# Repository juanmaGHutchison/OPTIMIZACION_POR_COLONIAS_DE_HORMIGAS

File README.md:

# Proyecto Final de Carrera: Diseño y Fabricación de Robots basados en Arduino para realizar el Algoritmo de Colonias de Hormigas.

_El proyecto permite realizar una ejecución real del Algoritmo de Colonias de Hormigas en un robot diseñado y fabricado en Arduino, diseño del robot disponible en el mismo proyecto._

Podemos encontrar una breve explicación además de una ejecución del robot finalizado en el siguiente enlace:
* [Ejecución ACO en Arduino](https://www.youtube.com/watch?v=iJVlAWncoFY&t=352s) - Video explicativo con posterior ejecución del Algoritmo de Colonias de Hormigas.

Y tenemos otro video en el cual se detalla el montaje de dicho robot en Arduino:
* [Montaje robot ACO](https://www.youtube.com/watch?v=88lnHN8jg98) - Video explicativo del montaje del robot en Arduino.

## Descripcion de directorios y archivos

_Descripción de los directorios y archivos disponibles en el proyecto:_

* 'ACO_CPP': En este directorio se encuentran los archivos necesarios para ejecutar el Algoritmo de Colonias de Hormigas en el lenguaje C++. De este programa se ha realizado gran parte de la experimentación del archivo 'Gomez-Hutchison-JuanManuel_TFG' Capítulo 4.
* 'ACOv2_robot': En este directorio se encuentra el proyecto final realizado en Arduino el cual se cargará físicamente al Robot.
* 'ACOv2_servidor': En este directorio se encuentra la parte del servidor, el cual se encargará, entre otras funciones de comunicar a las hormigas y actualizar las feromonas del mapa.
* 'BLUETOOTH_PRUEBA': En este directorio se encuentra un código simple para testear la comunicación Bluetooth entre el Robot y el servidor.
* 'CNYboardV2.0': Directorio donde se almacena el proyecto de diseño de la PCB al que irán conectados los sensores CNY70. Podemos encontrar la información en la documentación del archivo 'Gomez-Hutchison-JuanManuel_TFG', Sección 3.3.4.1.
* 'TEST_PIEZAS_HORMIGAS': Directorio que contiene código en Arduino para el testeo de piezas individuales del Robot, sensores, actuadores... así como de algunas pruebas de integración de éstos. 
* 'shieldV2.0.1': Directorio donde se almacena el proyecto de diseño de la PCB al que irán interconectados todos los componentes electrónicos. Podemos encontrar la información en la documentación del archivo 'Gomez-Hutchison-JuanManuel_TFG', Sección 3.3.4.2.
* 'Diseño_soporte3D': Directorio que contiene el diseño del soporte de la batería de nuestro robot.
* 'Mapa': Directorior que contiene el diseño del mapa así como las imágenes listas para imprimir.
* 'Gomez-Hutchison-JuanManuel_TFG': Archivo que contiene la documentación completa del proyecto, para cualquier tipo de duda referente al proyecto, acceder a este archivo.

### Pre-requisitos 

_Que cosas necesitas para instalar el software:_

* Arduino IDE en su última versión.
* Qt creator v4.4.10 o superior.
* Opcional: Compilador clang++ para ejecución del código en C++. Compilado con Makefile.

### Instalación 

_Simplemente tendremos que cargar el código en Arduino en el robot una vez fabricado, imprimir el mapa sobre el que se lanzará al Robot, y en un PC el código del servidor creado en Qt._

## Ejecutando las pruebas 

_Para la obtención de resultados iniciamos el servidor en Qt, lanzamos el Robot en el mapa y seguimos los pasos descritos en el documento 'Gomez-Hutchison-Juanmanuel_TFG' en la Sección 3.10_

### Analice las pruebas end-to-end 

_Los resultados de las pruebas realizadas y contrastadas a la vez que justificadas las encontramos en el documento 'Gomez-Hutchison-Juanmanuel_TFG' en el Capítulo 4_

## Construido con 

_Herramientas utilizadas para el proyecto_

* [Qt creator](https://www.qt.io/product/development-tools) - Usado para hacer el programa servidor.
* [Arduino IDE](https://www.arduino.cc/) - Usado para hacer el programa del Robot en Arduino 
* [Clang](https://clang.llvm.org/) - Usado para compilar el Programa en C++
* [GnuPlot](http://www.gnuplot.info/) - Usado para generar Gráficas
* [Eagle](https://www.autodesk.com/products/eagle/overview?plc=F360&term=1-YEAR&support=ADVANCED&quantity=1) - Usado para realizar el diseño de las PCB
* [Fusion 360](https://www.autodesk.es/products/fusion-360/overview?term=1-YEAR) - Usado para realizar el diseño 3D
* [InkScape](https://inkscape.org/es/) - Usado para el diseño del mapa
* [Latex](https://es.overleaf.com) - Usado para escribir la documentación.

## Autores 

_Ayudas ofrecidas_

* **Arturo Morgado Estévez** - *Estructuración del proyecto y electrónica*
* **Abel García Otero** - *Electrónica*
* **Ignacio Díaz Cano** - *Documentación y codificación* - [ignaciodc](https://github.com/ignaciodc)

---
Realizado por [juanmaGHutchison](https://github.com/juanmaGHutchison)

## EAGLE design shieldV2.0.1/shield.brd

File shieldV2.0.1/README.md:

# Diseño de Circuito Impreso para la interconexión de componentes.

_Proyecto realizado en Eagle donde se muestran los esquemáticos y el diseño de dicho esquemático donde se interconectan los componentes electrónicos._

## Descripción de archivos del directorio

_Descripción de los archivos principales de este directorio:_

* 'shield.brd': Diseño del circuito impreso.
* 'shield.pdf': PDF donde se muestra el diseño realizado en el archivo 'shield.brd'.
* 'shield.sch': Esquemático del circuito impreso.
* 'shield.pdf': PDF donde se muestra el esquemático realizado en el archivo 'shield.sch'.
* 'eagle.epf': Archivo de tipo proyecto, el cual abrira los archivos en el programa Eagle.

### Pre-requisitos 

_Que cosas necesitas para instalar el software:_

* Autodesk Eagle en su última versión.

## Ejecutando las pruebas 

_PCB totalmente testeada tanto por software con la herramienta DRC, tanto impresa, de manera empírica._

## Construido con 

_Herramientas utilizadas para el proyecto_

* [Eagle](https://www.autodesk.com/products/eagle/overview?plc=F360&term=1-YEAR&support=ADVANCED&quantity=1) - Usado para realizar el diseño de las PCB

---
Realizado por [juanmaGHutchison](https://github.com/juanmaGHutchison)

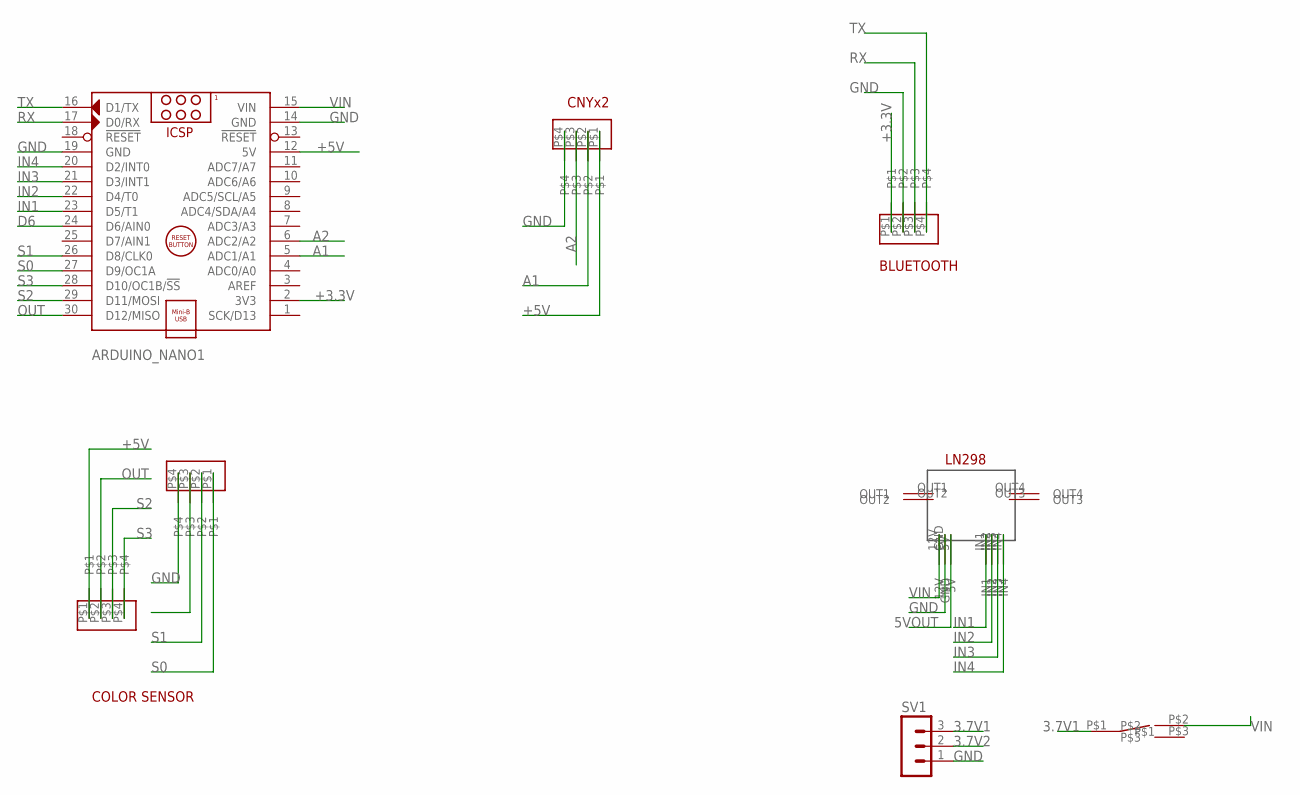
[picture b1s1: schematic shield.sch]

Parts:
ARDUINO_NANO1: ARDUINO_NANO
SV1: MA03-1
U$1, U$2, U$4, U$6: PIN4
U$3: INTERRUPTOR
U$5: LN298V2

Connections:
3.7V1: SV1.3, U$3.P$1
3.7V2: SV1.2
5VOUT: U$5.5V
+3.3V: ARDUINO_NANO1.2 (3V3), U$1.P$1
+5V: ARDUINO_NANO1.12 (5V), U$2.P$1, U$6.P$1
A1: ARDUINO_NANO1.5 (ADC1/A1), U$6.P$2
A2: ARDUINO_NANO1.6 (ADC2/A2), U$6.P$3
D6: ARDUINO_NANO1.24 (D6/AIN0)
GND: ARDUINO_NANO1.14 (GND), ARDUINO_NANO1.19 (GND), SV1.1, U$1.P$2, U$4.P$4, U$5.GND, U$6.P$4
IN1: ARDUINO_NANO1.23 (D5/T1), U$5.IN1
IN2: ARDUINO_NANO1.22 (D4/T0), U$5.IN2
IN3: ARDUINO_NANO1.21 (D3/INT1), U$5.IN3
IN4: ARDUINO_NANO1.20 (D2/INT0), U$5.IN4
OUT: ARDUINO_NANO1.30 (D12/MISO), U$2.P$2
RX: ARDUINO_NANO1.17 (D0/RX), U$1.P$3
S0: ARDUINO_NANO1.27 (D9/OC1A), U$4.P$1
S1: ARDUINO_NANO1.26 (D8/CLK0), U$4.P$2
S2: ARDUINO_NANO1.29 (D11/MOSI), U$2.P$3
S3: ARDUINO_NANO1.28 (D10/OC1B/!SS), U$2.P$4
TX: ARDUINO_NANO1.16 (D1/TX), U$1.P$4
VIN: ARDUINO_NANO1.15 (VIN), U$3.P$2, U$5.12V

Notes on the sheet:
BLUETOOTH
COLOR SENSOR
CNYx2

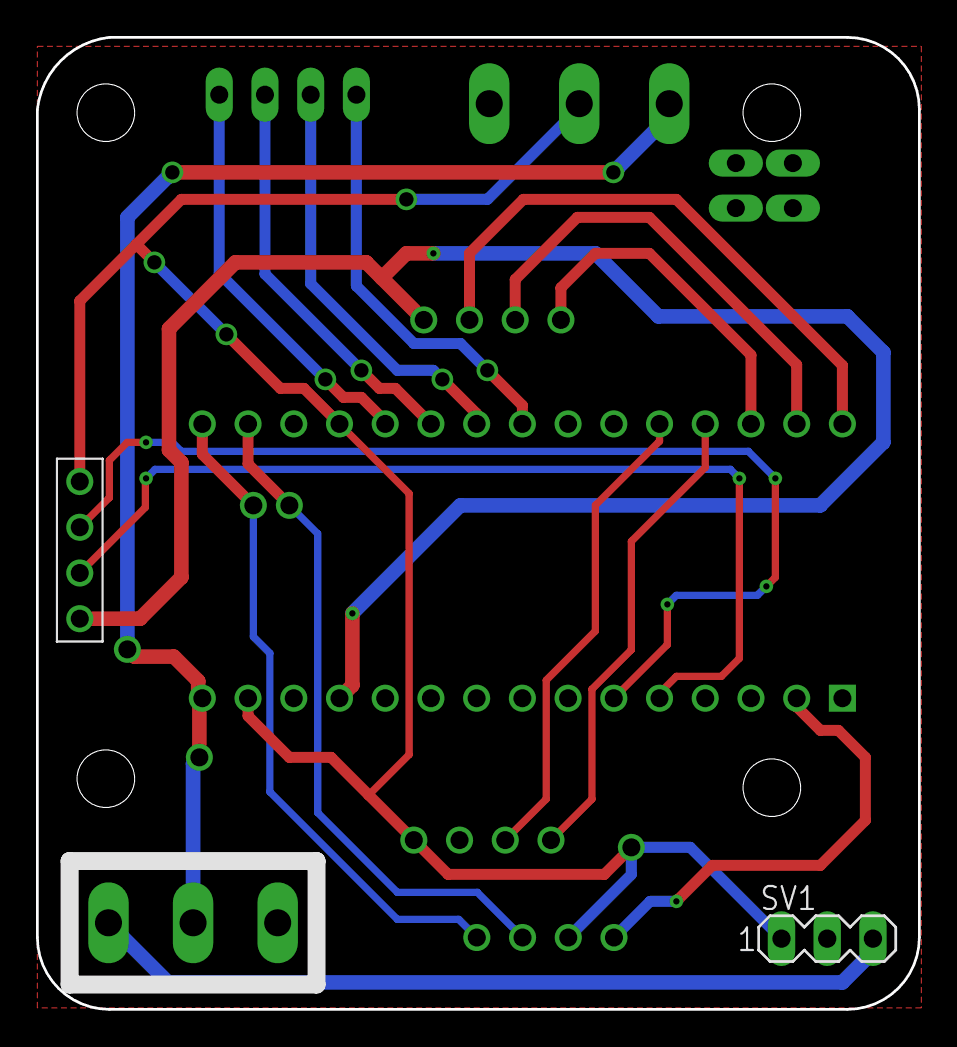
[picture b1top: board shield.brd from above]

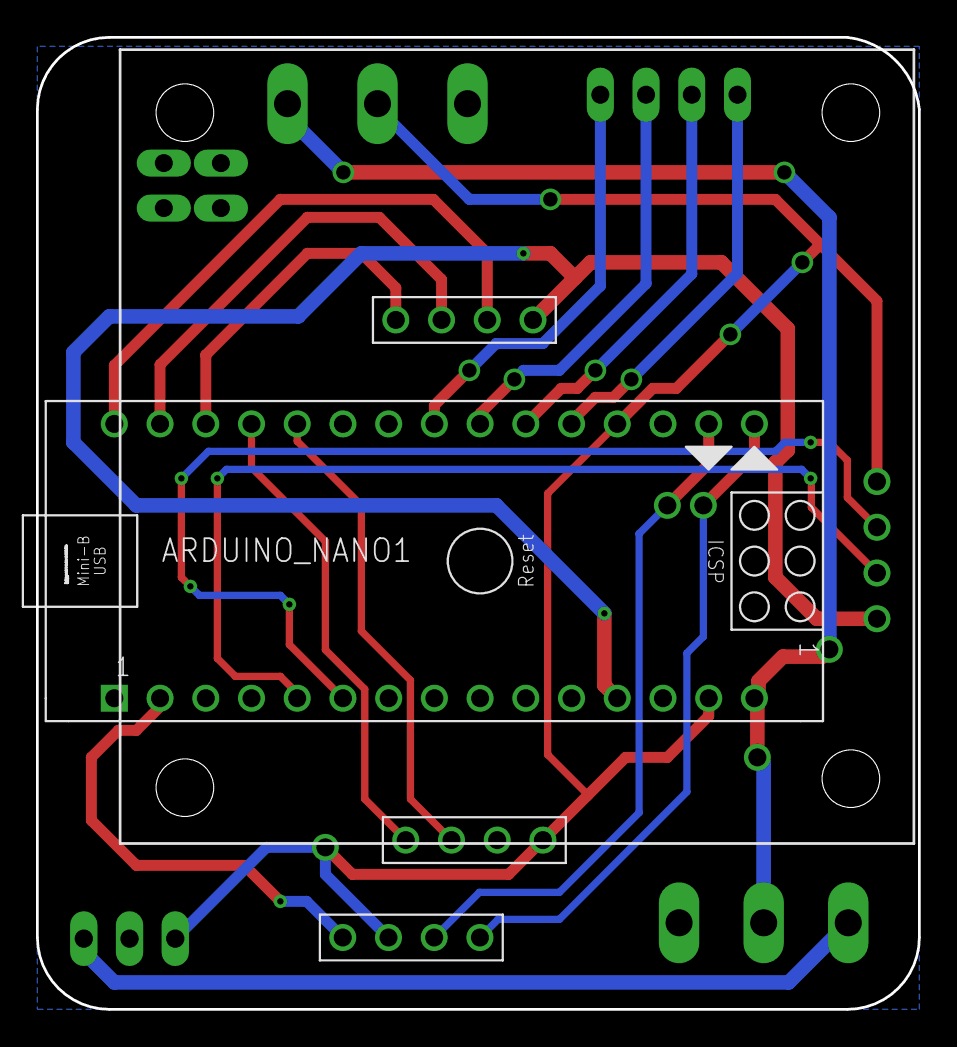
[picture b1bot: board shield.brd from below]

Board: 2 copper layers, 49.0 x 54.0 mm, 8 parts (5 on the bottom side), 18 nets.

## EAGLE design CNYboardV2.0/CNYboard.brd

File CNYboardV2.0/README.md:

# Diseño de Circuito Impreso para sensores CNY70.

_Proyecto realizado en Eagle donde se muestran los esquemáticos y el diseño de dicho esquemático donde se interconectan los sensores ópticos infrarrojos CNY70._

## Descripción de archivos del directorio

_Descripción de los archivos principales de este directorio:_

* 'CNYboard.brd': Diseño del circuito impreso.
* 'CNYboard.pdf': PDF donde se muestra el diseño realizado en el archivo 'CNYboard.brd'.
* 'CNYboard.sch': Esquemático del circuito impreso.
* 'CNYboard.pdf': PDF donde se muestra el esquemático realizado en el archivo 'CNYboard.sch'.
* 'eagle.epf': Archivo de tipo proyecto, el cual abrira los archivos en el programa Eagle.

### Pre-requisitos 

_Que cosas necesitas para instalar el software:_

* Autodesk Eagle en su última versión.

## Ejecutando las pruebas 

_PCB totalmente testeada tanto por software con la herramienta DRC, tanto impresa, de manera empírica._

## Construido con 

_Herramientas utilizadas para el proyecto_

* [Eagle](https://www.autodesk.com/products/eagle/overview?plc=F360&term=1-YEAR&support=ADVANCED&quantity=1) - Usado para realizar el diseño de las PCB

---
Realizado por [juanmaGHutchison](https://github.com/juanmaGHutchison)

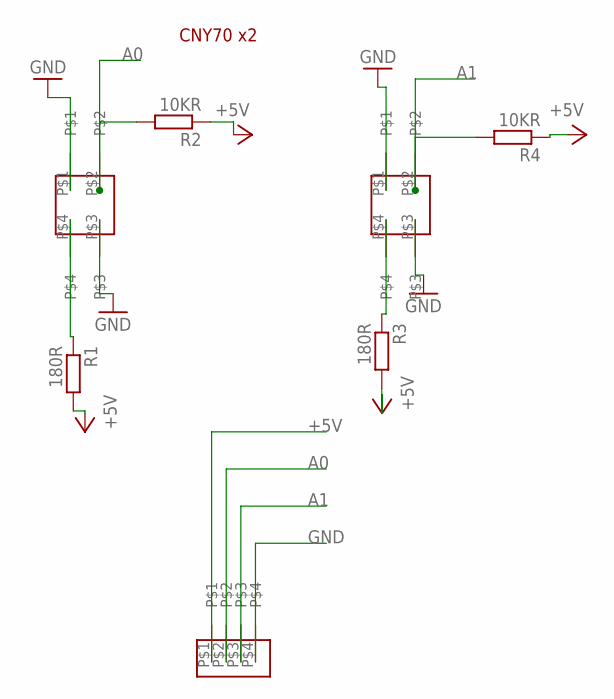
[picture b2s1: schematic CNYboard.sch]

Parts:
R1, R3: 180R; R0603
R2, R4: 10KR; R0603
U$1, U$2: CNYSOKET
U$3: PIN4

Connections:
+5V: R1.2, R2.1, R3.2, R4.1, U$3.P$1
A0: R2.2, U$1.P$2, U$3.P$2
A1: R4.2, U$2.P$2, U$3.P$3
GND: U$1.P$1, U$1.P$3, U$2.P$1, U$2.P$3, U$3.P$4
unnamed: R1.1, U$1.P$4
unnamed: R3.1, U$2.P$4

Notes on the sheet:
CNY70 x2

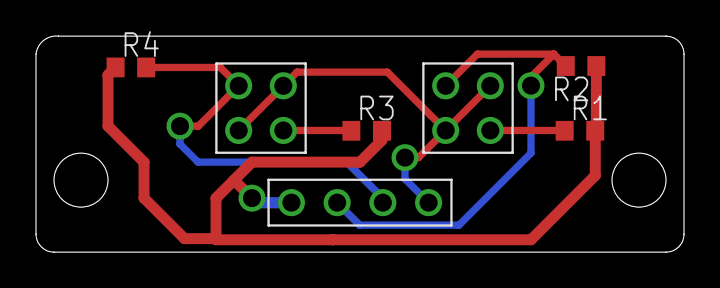
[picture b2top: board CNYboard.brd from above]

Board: 2 copper layers, 36.0 x 12.0 mm, 7 parts (0 on the bottom side), 6 nets.

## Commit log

2021-04-18 first commit, and stable version
2021-04-18 Documentacion GIT
2021-04-19 correccion errata reame md
2021-04-28 Diseño 3D y actualización de pines
2021-04-30 Subida del mapa y actualización README.md
2021-04-30 Readme.md youtube
